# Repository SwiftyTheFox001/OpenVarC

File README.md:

# OpenVarC
OSHW Variable Capacitor based on PCBs

This project intends to find a viable alternative for the variable capacitors for high voltages that got rare in modern electronics, but are still in demand for ham radio operators for various projects. At the moment this project is still in "beta phase" covers only one size of cap and some specs are still to be tested like the max. AC voltage capability. Please consider this while rebuilding a capacitor.

Features:
- Modular
- Uses PCBs and easily available mechanic parts (metric screws, washers & nuts)
- at least 2kV 
- Holes for light barrier to allow automatic centering

Future development:
- different sizes
- measuring max. Voltage capability
- optimizing the center tapped 

On ordering the PCBs:
- Thickness: 0.8mm
- Amount of PCBs: use calculations.ods to calculate the approximate amount of needed stacks and order a bit more. The amount depends on the dielectric properties of the used FR4 material. Milage may vary!

What you need for the large VarCs:
- Stator plate PCBs
- Rotor plate PCBs
- 4x M4 threaded rods of the same length
- 16x M4 Nuts
- M4 Washers (4 between 2 stators)
- 8mm rectangular aluminium extrusion (Axis) Note: Can be a U-shaped extrusion as well
- Cable shoes that fit on the M4 threaded rod
- 3D printed parts:
  - 2x H750.stl
  - 1x H751_1.stl
  - 1x H751_2.stl
- a Saw 

Assembly:
1) Lengthen the rectrangular axis and the 4 threaded rods depending on your need. Calculate some extra length to ensure that you can add a few stacks later if needed
2) put one M4 Nut min. 1cm from the ends of each threaded rod
3) Stack the PCBs the following way:
- Slide stator plate with silk screen showing upside (text/markings) on the four threaded rods
- First stack: put the axis inside the circular center hole of the stator plate
- Slide rotor plate with silk screen showing upside (text/markings) on the Axis
- Slide one washer on each of the threaded rods
- repeat the process with sliding a stator plate on top and ensure that the light barrier hole is aligned with the bottom layers
4) finishing the assembly
- ensure that all outside plates are stator plates
- put 4 M4 Nuts on top of thestack and tighten them carefully
- put the 3D printed parts 751_1 and 751_2 on both ends of the axis. Move the axis so, that the part 751_2 (endcap that prevents axis from going throuh) lies flush with the stator plate
- slide the two 3D printed parts 750 on the ends of the caps. Ensure that the light barrier holes are aligned
- slide the cable shoes on the threaded rods
- tighten with with M4 nuts

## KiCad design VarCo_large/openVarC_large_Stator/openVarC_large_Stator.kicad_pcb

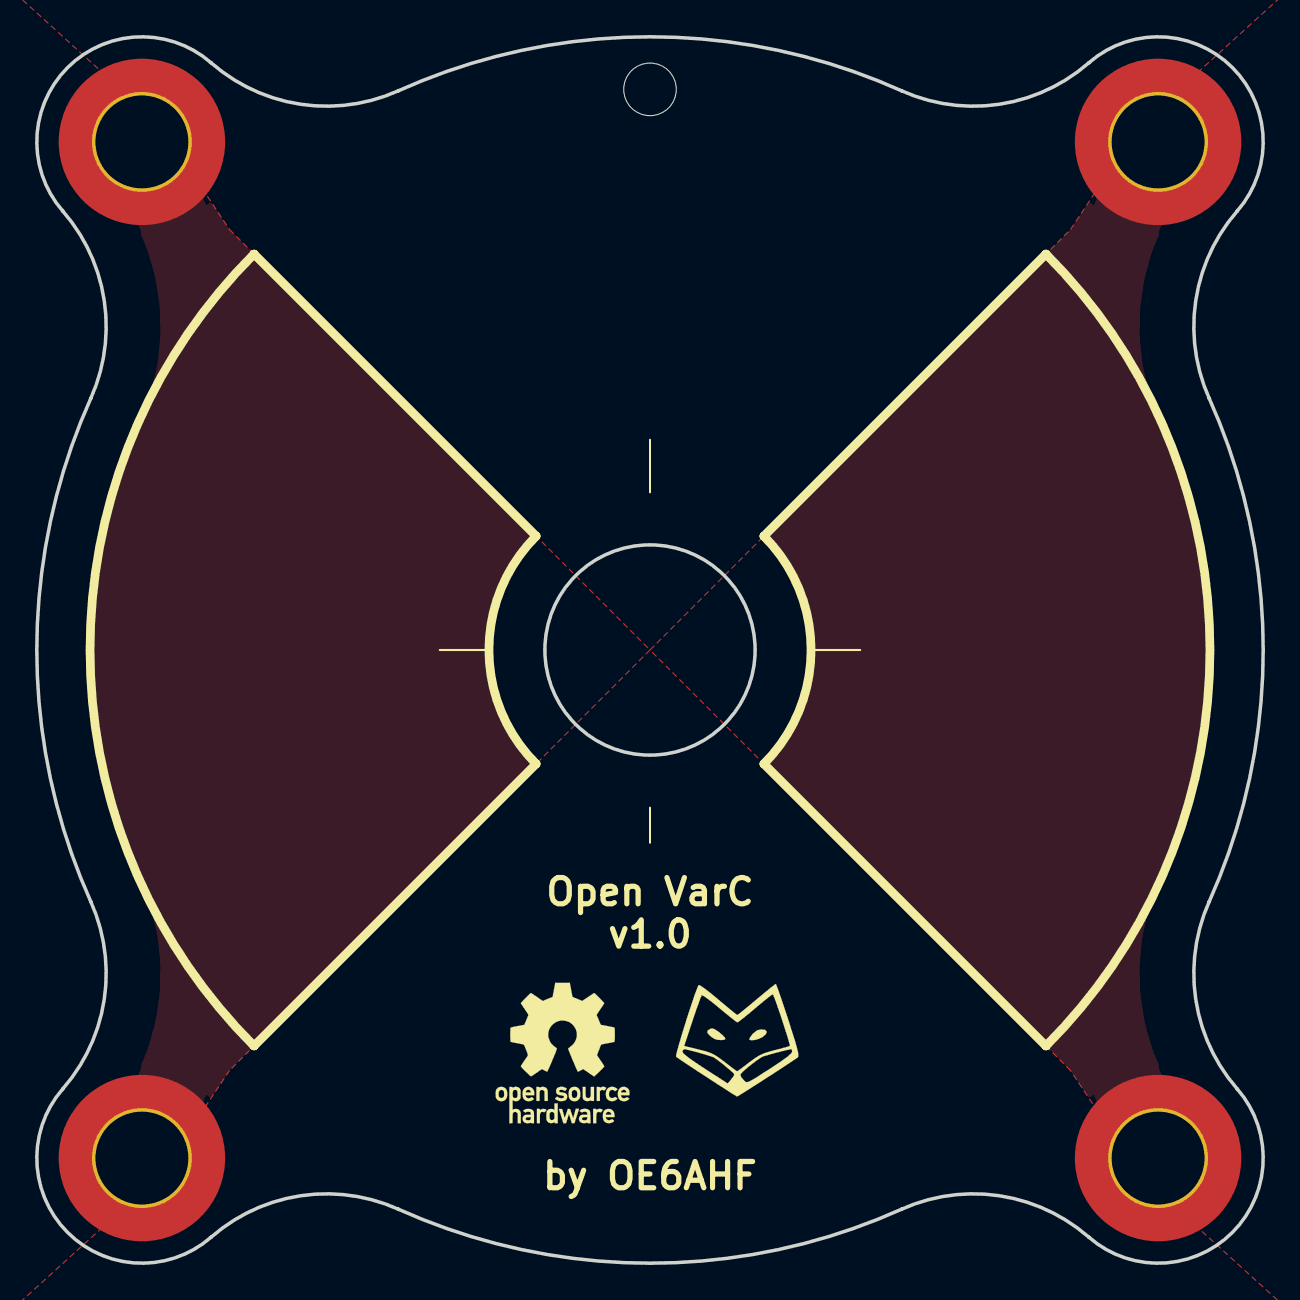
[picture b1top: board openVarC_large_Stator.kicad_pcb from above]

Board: 2 copper layers, 70.0 x 70.0 mm, 4 parts (0 on the bottom side), 2 nets, no tracks yet.

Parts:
H1, H2, H3, H4: MountingHole_Pad; MountingHole_5.3mm_M5_ISO7380_Pad_TopBottom

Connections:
/Side_A: H1.1, H2.1
/Side_B: H3.1, H4.1

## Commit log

2022-02-21 First Release
2022-02-21 Update License
    Set License to CC-BY-SA
2022-02-21 Added 3D Files
